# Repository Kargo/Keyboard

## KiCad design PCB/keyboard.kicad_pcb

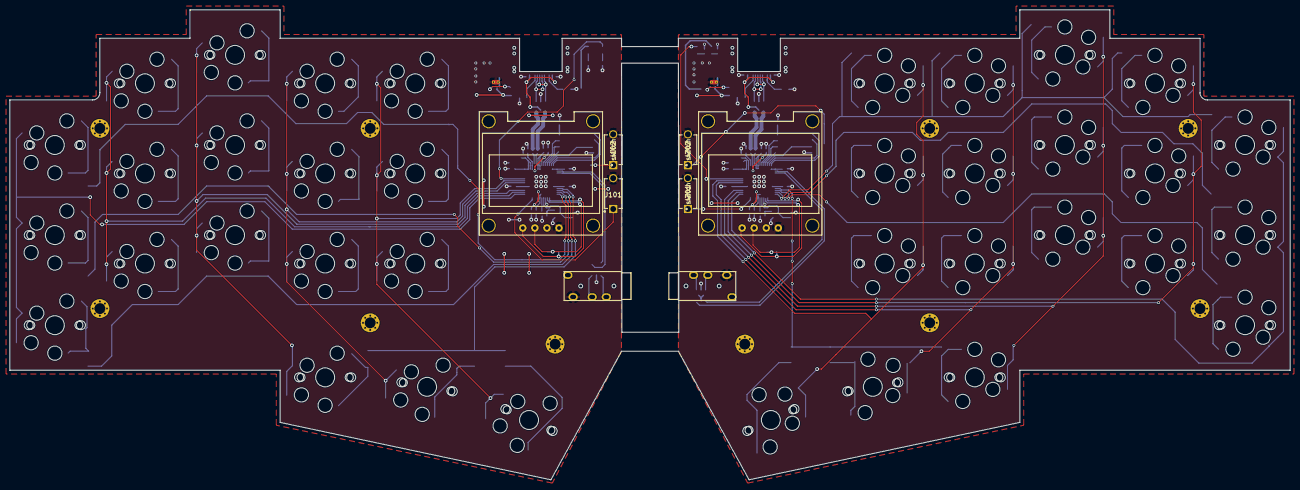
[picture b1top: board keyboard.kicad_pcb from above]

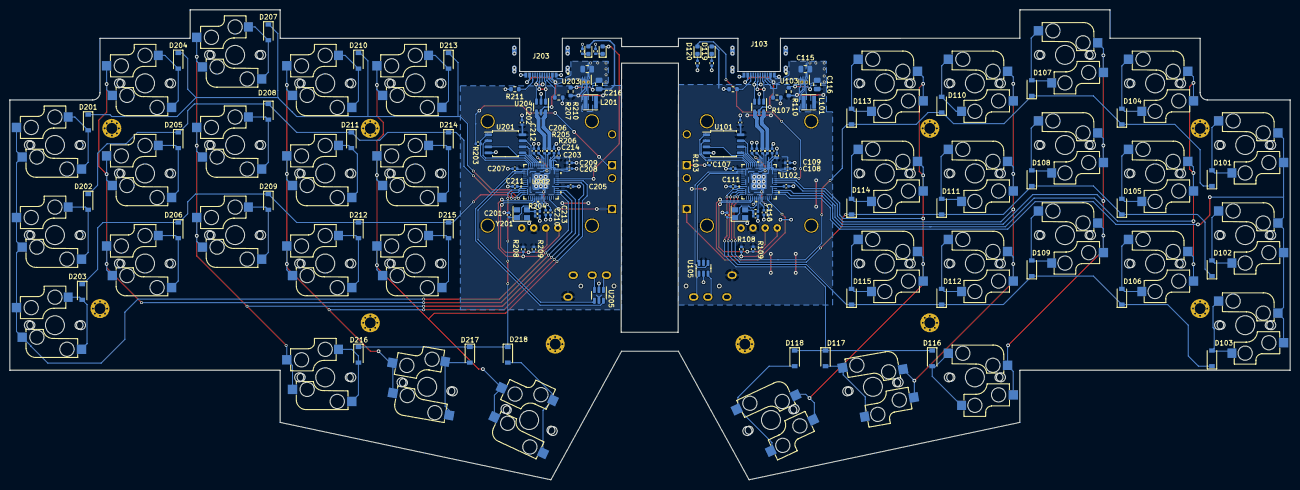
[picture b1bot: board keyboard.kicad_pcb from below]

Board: 2 copper layers, 270.0 x 99.1 mm, 164 parts (110 on the bottom side), 118 nets.

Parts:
C101, C104, C201, C204: 20p; C_0402_1005Metric
C102, C105, C106, C107, C108, C109, C110, C111, C112, C113, C202, C205, C206, C207, C208, C209, C210, C211, C212, C213: 100n; C_0402_1005Metric
C103, C114, C203, C214: 1u; C_0402_1005Metric
C115, C215: 10u; C_0805_2012Metric
C116, C216: 22uF; C_0805_2012Metric
D101, D102, D103, D104, D105, D106, D107, D108, D109, D110, D111, D112, D113, D114, D115, D116, D117, D118, D201, D202, D203, D204, D205, D206, D207, D208, D209, D210, D211, D212, D213, D214, D215, D216, D217, D218: DIODE; D_SOD-123
D119, D120, D219, D220: LED; LED_0603_1608Metric
H101, H102, H103, H104, H105, H201, H202, H203, H204, H205: MountingHole_Pad; M2_HOLE_v3
J101, J102, J201, J202: switch; SKHLACA010
J103, J203: USB4510-03-1-A_GCT; USB4510-03-1-A
J104, J204: CONN_DISPLAY; SSD1306_0.96_Oled
J105, J205: AudioJack4; TRRS-PJ-320A
L101, L201: 2.2μH; L_Taiyo-Yuden_NR-30xx
MX101, MX102, MX103, MX104, MX105, MX106, MX107, MX108, MX109, MX110, MX111, MX112, MX113, MX114, MX115, MX116, MX117, MX118, MX201, MX202, MX203, MX204, MX205, MX206, MX207, MX208, MX209, MX210, MX211, MX212, MX213, MX214, MX215, MX216, MX217, MX218: SW_Push; CherryMX_Choc_Hotswap
R101, R102, R201, R202: 2.2K; R_0402_1005Metric
R103, R104, R203, R204: 1k; R_0402_1005Metric
R105, R106, R205, R206: 27; R_0402_1005Metric
R107, R111, R207, R211: 5.1k; R_0603_1608Metric
R108, R109, R208, R209: 4.7K; R_0402_1005Metric
R110, R210: 100k; R_0603_1608Metric
U101, U201: W25Q128JVSIQ; SOIC-8_5.23x5.23mm_P1.27mm
U102, U202: RP2040; SC090813
U103, U203: TPS62172DSG; WSON-8-1EP_2x2mm_P0.5mm_EP0.9x1.6mm_ThermalVias
U104, U105, U204, U205: USBLC6-2SC6; SOT-23-6
Y101, Y201: 12MHz; Oscillator_SMD_Abracon_ASE-4Pin_3.2x2.5mm

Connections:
+1V1: C112.1, C113.1, C114.1, C212.1, C213.1, C214.1, U102.23 (DVDD), U102.45 (VREG_VOUT), U102.50 (DVDD), U202.23 (DVDD), U202.45 (VREG_VOUT), U202.50 (DVDD)
+3V3: C102.1, C103.1, C105.1, C106.1, C107.1, C108.1, C109.1, C110.1, C111.1, C116.1, C202.1, C203.1, C205.1, C206.1, C207.1, C208.1, C209.1, C210.1, C211.1, C216.1, D119.2 (A), D219.2 (A), J104.2, J105.S, J204.2, J205.S, L101.2, L201.2, R108.2, R109.2, R110.1, R208.2, R209.2, R210.1, U101.8 (VCC), U102.1 (IOVDD), U102.10 (IOVDD), U102.22 (IOVDD), U102.33 (IOVDD), U102.42 (IOVDD), U102.43 (ADC_AVDD), U102.44 (VREG_IN), U102.48 (USB_VDD), U102.49 (IOVDD), U103.6 (VOS), U105.5 (VBUS), U201.8 (VCC), U202.1 (IOVDD), U202.10 (IOVDD), U202.22 (IOVDD), U202.33 (IOVDD), U202.42 (IOVDD), U202.43 (ADC_AVDD), U202.44 (VREG_IN), U202.48 (USB_VDD), U202.49 (IOVDD), U203.6 (VOS), U205.5 (VBUS), Y101.4, Y201.4
/Left MCU/COL-1: MX101.1, MX102.1, MX103.1, U102.29 (GPIO18)
/Left MCU/COL-2: MX104.1, MX105.1, MX106.1, U102.30 (GPIO19)
/Left MCU/COL-3: MX107.1, MX108.1, MX109.1, MX116.1, U102.31 (GPIO20)
/Left MCU/COL-4: MX110.1, MX111.1, MX112.1, MX117.1, U102.35 (GPIO23)
/Left MCU/COL-5: MX113.1, MX114.1, MX115.1, MX118.1, U102.36 (GPIO24)
/Left MCU/D+: R105.2, U102.47 (USB_DP)
/Left MCU/D-: R106.2, U102.46 (USB_DM)
/Left MCU/LED: D120.2 (A), U102.37 (GPIO25)
/Left MCU/QSPI_SCLK: U101.6 (CLK), U102.52 (QSPI_SCLK)
/Left MCU/QSPI_SD0: U101.5 (DI(IO0)), U102.53 (QSPI_SD0)
/Left MCU/QSPI_SD1: U101.2 (DO(IO1)), U102.55 (QSPI_SD1)
/Left MCU/QSPI_SD2: U101.3 (IO2), U102.54 (QSPI_SD2)
/Left MCU/QSPI_SD3: U101.7 (IO3), U102.51 (QSPI_SD3)
/Left MCU/QSPI_SS: R103.1, U101.1 (~CS), U102.56 (QSPI_SS)
/Left MCU/ROW-1: D101.1 (K), D104.1 (K), D107.1 (K), D110.1 (K), D113.1 (K), U102.14 (GPIO11)
/Left MCU/ROW-2: D102.1 (K), D105.1 (K), D108.1 (K), D111.1 (K), D114.1 (K), U102.13 (GPIO10)
/Left MCU/ROW-3: D103.1 (K), D106.1 (K), D109.1 (K), D112.1 (K), D115.1 (K), U102.12 (GPIO9)
/Left MCU/ROW-4: D116.1 (K), D117.1 (K), D118.1 (K), U102.11 (GPIO8)
/Left MCU/RX: U102.3 (GPIO1), U105.6 (I/O1)
/Left MCU/SCL: J104.3, R109.1, U102.18 (GPIO15)
/Left MCU/SDA: J104.4, R108.1, U102.17 (GPIO14)
/Left MCU/TX: U102.2 (GPIO0), U105.4 (I/O2)
/Left MCU/USB_CONN_D+: J103.A6 (DP1), J103.B6 (DP2), U104.3 (I/O2)
/Left MCU/USB_CONN_D-: J103.A7 (DN1), J103.B7 (DN2), U104.1 (I/O1)
/Left MCU/USB_D+: R105.1, U104.4 (I/O2)
/Left MCU/USB_D-: R106.1, U104.6 (I/O1)
/Left MCU/XIN: C101.1, U102.20 (XIN), Y101.1
/Left MCU/XOUT: R104.1, U102.21 (XOUT)
/Left MCU/~BOOTSEL: J102.1, R103.2
/Left MCU/~RESET: J101.1, U102.26 (RUN)
/Right MCU/COL-1: MX201.1, MX202.1, MX203.1, U202.29 (GPIO18)
/Right MCU/COL-2: MX204.1, MX205.1, MX206.1, U202.30 (GPIO19)
/Right MCU/COL-3: MX207.1, MX208.1, MX209.1, MX216.1, U202.31 (GPIO20)
/Right MCU/COL-4: MX210.1, MX211.1, MX212.1, MX217.1, U202.35 (GPIO23)
/Right MCU/COL-5: MX213.1, MX214.1, MX215.1, MX218.1, U202.36 (GPIO24)
/Right MCU/D+: R205.2, U202.47 (USB_DP)
/Right MCU/D-: R206.2, U202.46 (USB_DM)
/Right MCU/LED: D220.2 (A), U202.37 (GPIO25)
/Right MCU/QSPI_SCLK: U201.6 (CLK), U202.52 (QSPI_SCLK)
/Right MCU/QSPI_SD0: U201.5 (DI(IO0)), U202.53 (QSPI_SD0)
/Right MCU/QSPI_SD1: U201.2 (DO(IO1)), U202.55 (QSPI_SD1)
/Right MCU/QSPI_SD2: U201.3 (IO2), U202.54 (QSPI_SD2)
/Right MCU/QSPI_SD3: U201.7 (IO3), U202.51 (QSPI_SD3)
/Right MCU/QSPI_SS: R203.1, U201.1 (~CS), U202.56 (QSPI_SS)
/Right MCU/ROW-1: D201.1 (K), D204.1 (K), D207.1 (K), D210.1 (K), D213.1 (K), U202.14 (GPIO11)
/Right MCU/ROW-2: D202.1 (K), D205.1 (K), D208.1 (K), D211.1 (K), D214.1 (K), U202.13 (GPIO10)
/Right MCU/ROW-3: D203.1 (K), D206.1 (K), D209.1 (K), D212.1 (K), D215.1 (K), U202.12 (GPIO9)
/Right MCU/ROW-4: D216.1 (K), D217.1 (K), D218.1 (K), U202.11 (GPIO8)
/Right MCU/RX: U202.3 (GPIO1), U205.4 (I/O2)
/Right MCU/SCL: J204.3, R209.1, U202.18 (GPIO15)
/Right MCU/SDA: J204.4, R208.1, U202.17 (GPIO14)
/Right MCU/TX: U202.2 (GPIO0), U205.6 (I/O1)
/Right MCU/USB_CONN_D+: J203.A6 (DP1), J203.B6 (DP2), U204.3 (I/O2)
/Right MCU/USB_CONN_D-: J203.A7 (DN1), J203.B7 (DN2), U204.1 (I/O1)
/Right MCU/USB_D+: R205.1, U204.4 (I/O2)
/Right MCU/USB_D-: R206.1, U204.6 (I/O1)
/Right MCU/XIN: C201.1, U202.20 (XIN), Y201.1
/Right MCU/XOUT: R204.1, U202.21 (XOUT)
/Right MCU/~BOOTSEL: J202.1, R203.2
/Right MCU/~RESET: J201.1, U202.26 (RUN)
/TRRS Connection/L_RX_CONN: J105.R2, U105.1 (I/O1)
/TRRS Connection/L_TX_CONN: J105.R1, U105.3 (I/O2)
/TRRS Connection/R_RX_CONN: J205.R1, U205.3 (I/O2)
/TRRS Connection/R_TX_CONN: J205.R2, U205.1 (I/O1)
GND: C101.2, C102.2, C103.2, C104.2, C105.2, C106.2, C107.2, C108.2, C109.2, C110.2, C111.2, C112.2, C113.2, C114.2, C115.2, C116.2, C201.2, C202.2, C203.2, C204.2, C205.2, C206.2, C207.2, C208.2, C209.2, C210.2, C211.2, C212.2, C213.2, C214.2, C215.2, C216.2, J101.2, J102.2, J103.A1-B12 (GND), J103.B1-A12 (GND), J104.1, J105.T, J201.2, J202.2, J203.A1-B12 (GND), J203.B1-A12 (GND), J204.1, J205.T, R101.1, R102.1, R107.2, R111.1, R201.1, R202.1, R207.2, R211.1, U101.4 (GND), U102.19 (TESTEN), U102.57 (GND), U103.1 (PGND), U103.4 (AGND), U103.5 (FB), U103.9 (PAD), U104.2 (GND), U105.2 (GND), U201.4 (GND), U202.19 (TESTEN), U202.57 (GND), U203.1 (PGND), U203.4 (AGND), U203.5 (FB), U203.9 (PAD), U204.2 (GND), U205.2 (GND), Y101.2, Y201.2
unnamed: C104.1, R104.2, Y101.3
unnamed: C204.1, R204.2, Y201.3
unnamed: D101.2 (A), MX101.2
unnamed: D102.2 (A), MX102.2
unnamed: D103.2 (A), MX103.2
unnamed: D104.2 (A), MX104.2
unnamed: D105.2 (A), MX105.2
unnamed: D106.2 (A), MX106.2
unnamed: D107.2 (A), MX107.2
unnamed: D108.2 (A), MX108.2
unnamed: D109.2 (A), MX109.2
unnamed: D110.2 (A), MX110.2
unnamed: D111.2 (A), MX111.2
unnamed: D112.2 (A), MX112.2
unnamed: D113.2 (A), MX113.2
unnamed: D114.2 (A), MX114.2
unnamed: D115.2 (A), MX115.2
unnamed: D116.2 (A), MX116.2
unnamed: D117.2 (A), MX117.2
unnamed: D118.2 (A), MX118.2
unnamed: D119.1 (K), R101.2
unnamed: D120.1 (K), R102.2
unnamed: D201.2 (A), MX201.2
unnamed: D202.2 (A), MX202.2
unnamed: D203.2 (A), MX203.2
unnamed: D204.2 (A), MX204.2
unnamed: D205.2 (A), MX205.2
unnamed: D206.2 (A), MX206.2
unnamed: D207.2 (A), MX207.2
unnamed: D208.2 (A), MX208.2
unnamed: D209.2 (A), MX209.2
unnamed: D210.2 (A), MX210.2
unnamed: D211.2 (A), MX211.2
unnamed: D212.2 (A), MX212.2
unnamed: D213.2 (A), MX213.2
unnamed: D214.2 (A), MX214.2
unnamed: D215.2 (A), MX215.2
unnamed: D216.2 (A), MX216.2
unnamed: D217.2 (A), MX217.2
unnamed: D218.2 (A), MX218.2
unnamed: D219.1 (K), R201.2
unnamed: D220.1 (K), R202.2
unnamed: J103.A5 (CC1), R107.1
unnamed: J103.B5 (CC2), R111.2
unnamed: J203.A5 (CC1), R207.1
unnamed: J203.B5 (CC2), R211.2
unnamed: L101.1, U103.7 (SW)
unnamed: L201.1, U203.7 (SW)
unnamed: R110.2, U103.8 (PG)
unnamed: R210.2, U203.8 (PG)
VBUS: C115.1, C215.1, J103.A4-B9 (VBUS), J103.B4-A9 (VBUS), J203.A4-B9 (VBUS), J203.B4-A9 (VBUS), U103.2 (VIN), U103.3 (EN), U104.5 (VBUS), U203.2 (VIN), U203.3 (EN), U204.5 (VBUS)

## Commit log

2022-11-07 Update footprint library
2022-11-13 wip full sch
2022-11-17 Layout done
2022-11-17 Remove unused file
2022-11-17 Update net labels
2022-11-21 latest changes
2022-11-21 Power and USB
2022-11-22 Swap usb pair
2022-11-22 More work on MCU
2022-11-22 remove some unused footprints
2022-11-22 add stagger, crude outline
2022-11-22 less crude outline
2022-11-23 Work
2022-11-23 Add mounting holes
2022-11-23 attempt duplicate
2022-11-24 Metric
2022-11-24 Add switch footprint
2022-11-25 add OLED footprint
2022-11-25 Update TRRS connector footprint
2022-11-25 Make board outline smaller
2022-11-25 Add rounded edge as test
2022-11-26 Left side 'done'
2022-11-26 More adjustments and space out trace
2022-11-26 Right ride
2022-12-10 fix errors
2022-12-19 Fix some warnings

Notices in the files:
parts and their libraries:
Copyright 2021 Accelerated Designs. All rights reserved.
